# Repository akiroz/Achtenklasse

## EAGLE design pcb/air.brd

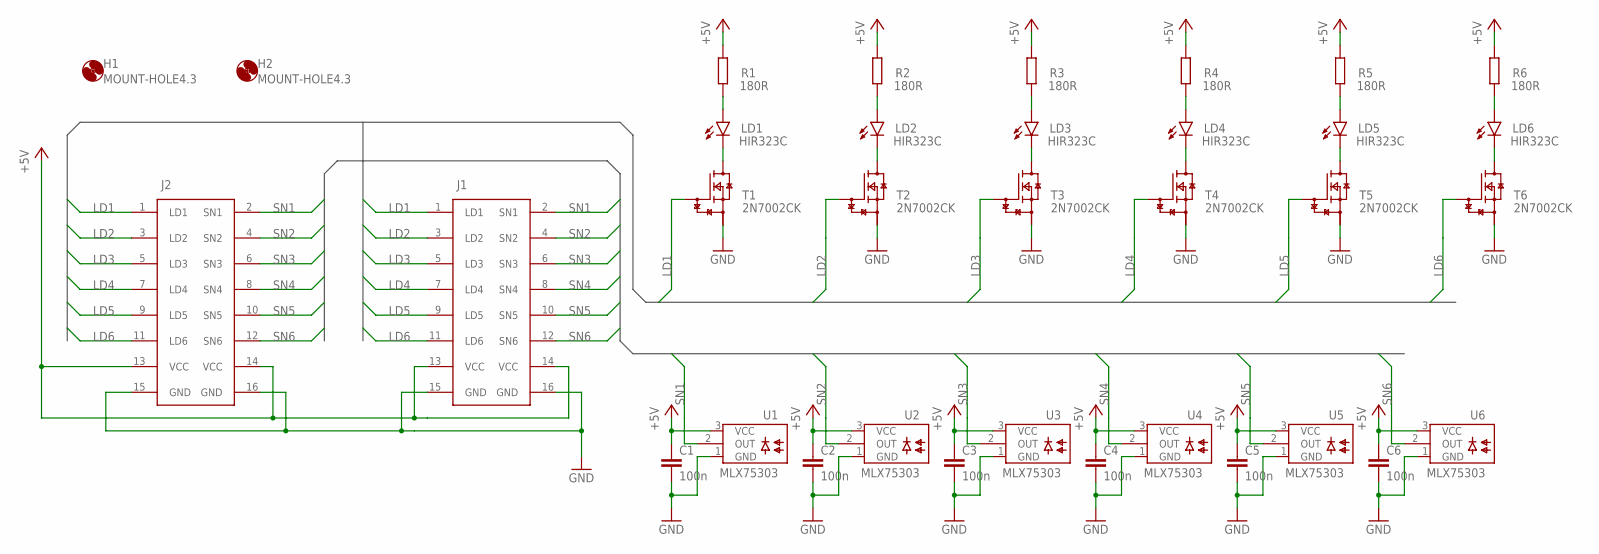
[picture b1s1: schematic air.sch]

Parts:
C1, C2, C3, C4, C5, C6: 100n; C0805K
H1, H2: MOUNT-HOLE4.3; 4,3
J1, J2: 2516-SMD-AIR; 612X1620621
LD1, LD2, LD3, LD4, LD5, LD6: HIR323C; LEDRD254W60D590H600B
R1, R2, R3, R4, R5, R6: 180R; R0805
T1, T2, T3, T4, T5, T6: 2N7002CK; SOT23
U1, U2, U3, U4, U5, U6: MLX75303; SOIC127P600X147-8N

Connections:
+5V: C1.1, C2.1, C3.1, C4.1, C5.1, C6.1, J1.13 (VCC), J1.14 (VCC), J2.13 (VCC), J2.14 (VCC), R1.2, R2.2, R3.2, R4.2, R5.2, R6.2, U1.3 (VCC), U2.3 (VCC), U3.3 (VCC), U4.3 (VCC), U5.3 (VCC), U6.3 (VCC)
GND: C1.2, C2.2, C3.2, C4.2, C5.2, C6.2, J1.15 (GND), J1.16 (GND), J2.15 (GND), J2.16 (GND), T1.2 (S), T2.2 (S), T3.2 (S), T4.2 (S), T5.2 (S), T6.2 (S), U1.1 (GND), U2.1 (GND), U3.1 (GND), U4.1 (GND), U5.1 (GND), U6.1 (GND)
LD1: J1.1 (LD1), J2.1 (LD1), T1.1 (G)
LD2: J1.3 (LD2), J2.3 (LD2), T2.1 (G)
LD3: J1.5 (LD3), J2.5 (LD3), T3.1 (G)
LD4: J1.7 (LD4), J2.7 (LD4), T4.1 (G)
LD5: J1.9 (LD5), J2.9 (LD5), T5.1 (G)
LD6: J1.11 (LD6), J2.11 (LD6), T6.1 (G)
unnamed: LD1.1 (A), R1.1
unnamed: LD1.2 (C), T1.3 (D)
unnamed: LD2.1 (A), R2.1
unnamed: LD2.2 (C), T2.3 (D)
unnamed: LD3.1 (A), R3.1
unnamed: LD3.2 (C), T3.3 (D)
unnamed: LD4.1 (A), R4.1
unnamed: LD4.2 (C), T4.3 (D)
unnamed: LD5.1 (A), R5.1
unnamed: LD5.2 (C), T5.3 (D)
unnamed: LD6.1 (A), R6.1
unnamed: LD6.2 (C), T6.3 (D)
SN1: J1.2 (SN1), J2.2 (SN1), U1.2 (OUT)
SN2: J1.4 (SN2), J2.4 (SN2), U2.2 (OUT)
SN3: J1.6 (SN3), J2.6 (SN3), U3.2 (OUT)
SN4: J1.8 (SN4), J2.8 (SN4), U4.2 (OUT)
SN5: J1.10 (SN5), J2.10 (SN5), U5.2 (OUT)
SN6: J1.12 (SN6), J2.12 (SN6), U6.2 (OUT)

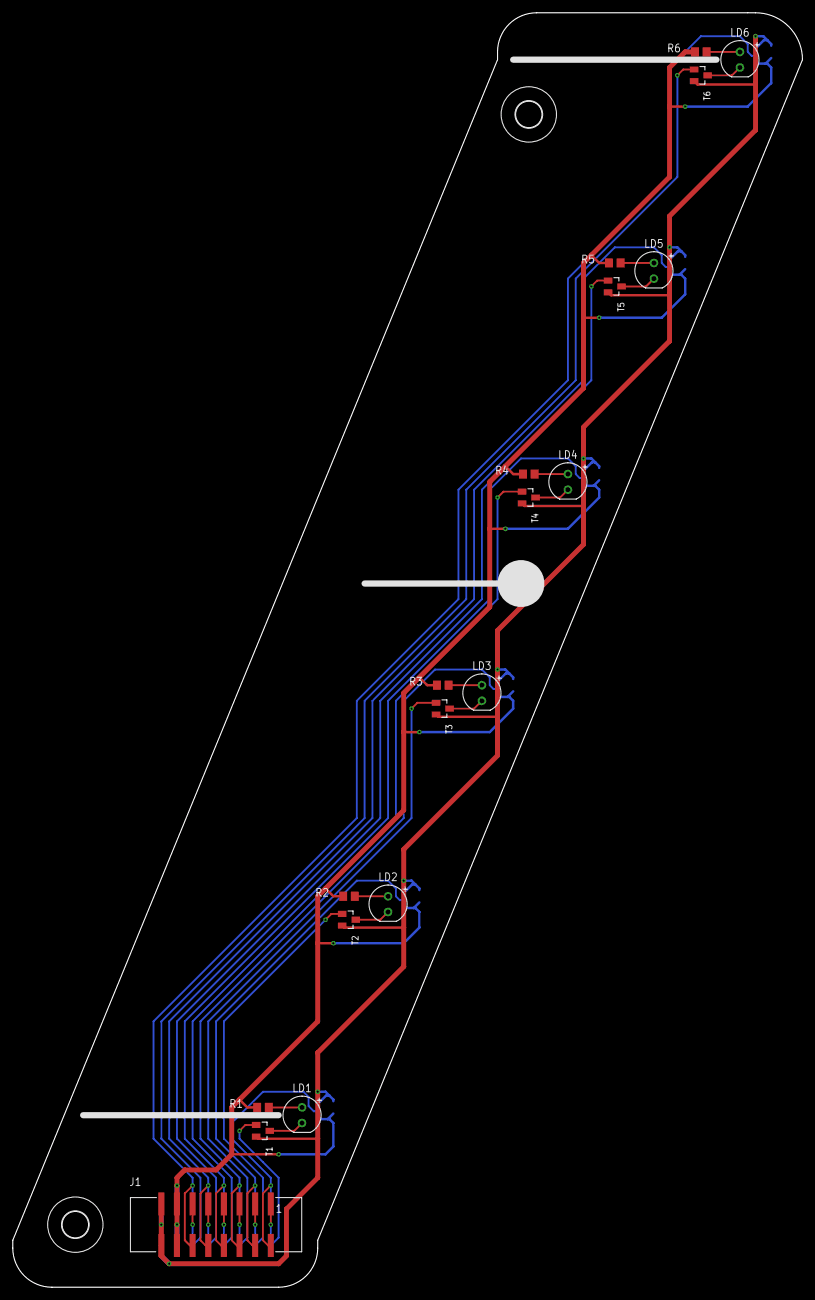
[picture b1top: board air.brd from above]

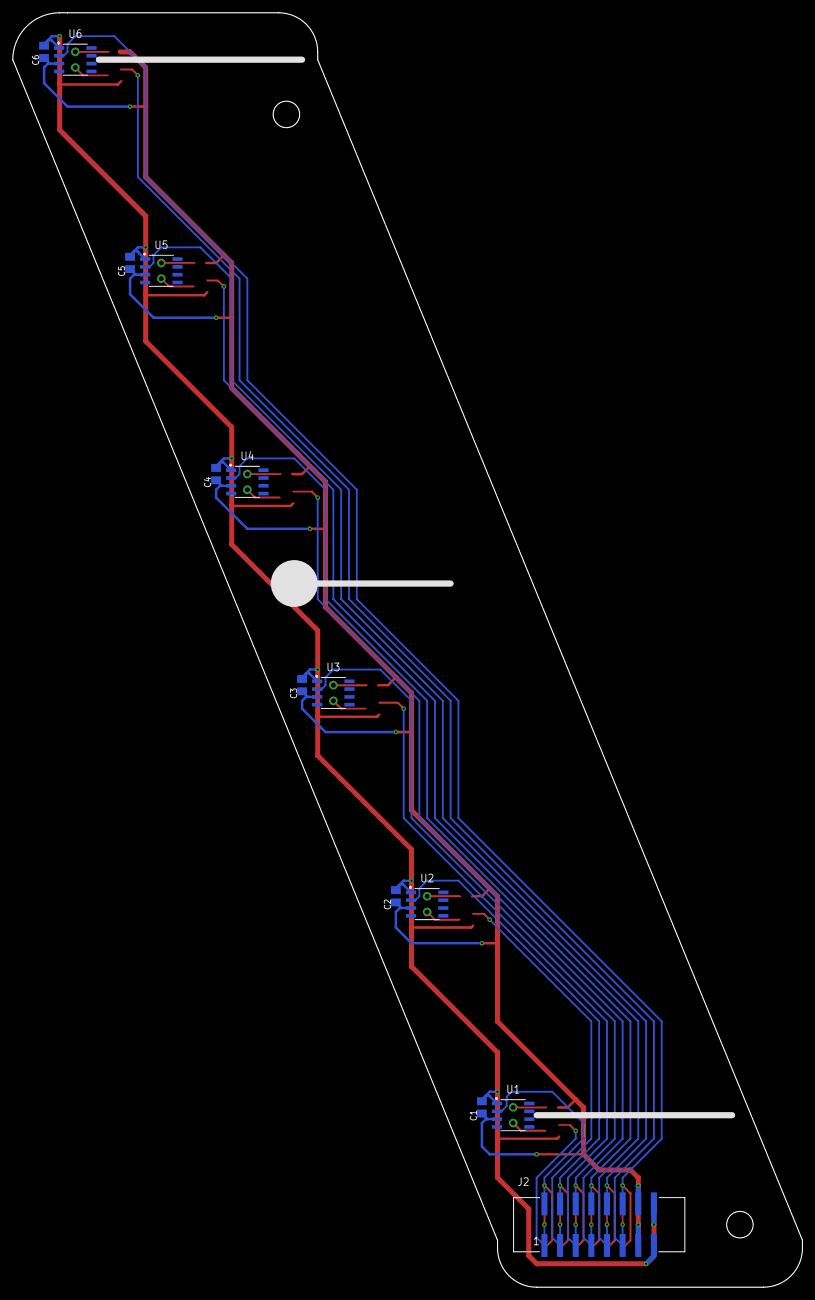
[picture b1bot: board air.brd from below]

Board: 2 copper layers, 128.3 x 207.0 mm, 34 parts (13 on the bottom side), 26 nets.

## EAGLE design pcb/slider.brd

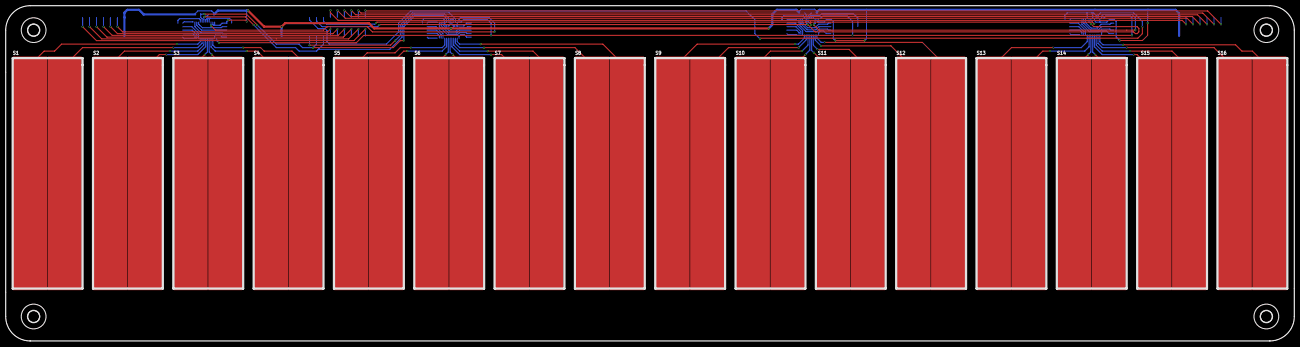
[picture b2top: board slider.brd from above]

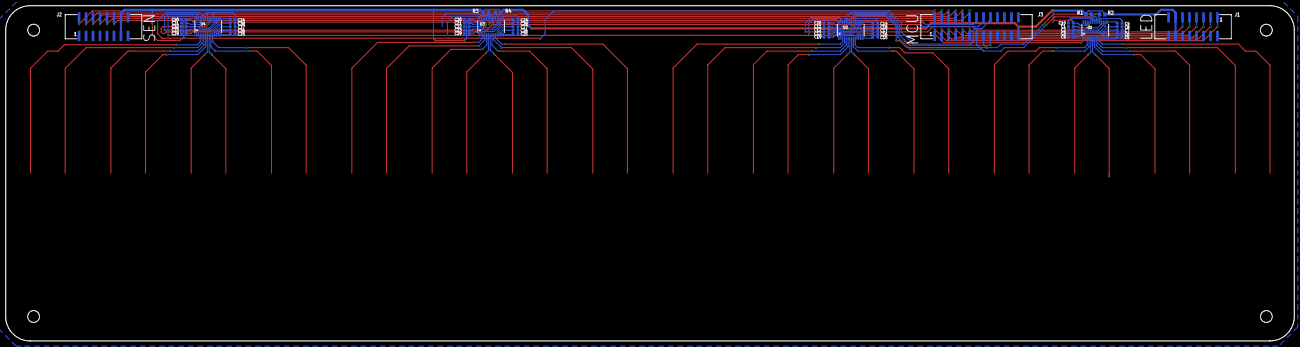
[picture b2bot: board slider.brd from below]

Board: 2 copper layers, 468.6 x 121.9 mm, 71 parts (51 on the bottom side), 91 nets.

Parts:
C1, C2, C3, C4, C5, C6, C7, C8, C9, C10, C11, C12, C13, C14, C15, C16, C17, C18, C19, C20, C21, C22, C23, C24, C25, C26, C27, C28, C29, C30, C31, C32, C33, C34, C35, C36, C37, C38, C39, C40: 100n; C0603K
H1, H2, H3, H4: MOUNT-HOLE4.3; 4,3
J1, J2: 612X1620621
J3: 612X2620621
R1, R2, R3, R4: 4.7k; R0805
S1, S2, S3, S4, S5, S6, S7, S8, S9, S10, S11, S12, S13, S14, S15, S16: SENSPAD
U1, U2, U3, U4: PCF8885TS; SOT361-1

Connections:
+5V: C10.1, C20.1, C30.1, C40.1, J1.13, J1.14, J2.13, J2.14, J3.25, R1.2, R2.2, R3.2, R4.2, U1.26, U1.27, U2.23, U2.26, U3.26, U3.27, U4.23, U4.26
GND: C1.2, C2.2, C3.2, C4.2, C5.2, C6.2, C7.2, C8.2, C9.2, C10.2, C11.2, C12.2, C13.2, C14.2, C15.2, C16.2, C17.2, C18.2, C19.2, C20.2, C21.2, C22.2, C23.2, C24.2, C25.2, C26.2, C27.2, C28.2, C29.2, C30.2, C31.2, C32.2, C33.2, C34.2, C35.2, C36.2, C37.2, C38.2, C39.2, C40.2, J1.15, J1.16, J2.15, J2.16, J3.26, U1.19, U1.22, U1.23, U1.24, U2.19, U2.22, U2.24, U3.19, U3.22, U3.23, U3.24, U4.19, U4.22, U4.24
INT1: J3.17, U2.25
INT2: J3.18, U4.25
LED1: J1.1, J3.1
LED2: J1.3, J3.3
LED3: J1.5, J3.5
LED4: J1.7, J3.7
LED5: J1.9, J3.9
LED6: J1.11, J3.11
unnamed: C1.1, U1.18
unnamed: C2.1, U1.17
unnamed: C3.1, U1.16
unnamed: C4.1, U1.15
unnamed: C5.1, U1.14
unnamed: C6.1, U1.13
unnamed: C7.1, U1.12
unnamed: C8.1, U1.11
unnamed: C11.1, U2.18
unnamed: C9.1, U1.2
unnamed: C12.1, U2.17
unnamed: C13.1, U2.16
unnamed: C14.1, U2.15
unnamed: C15.1, U2.14
unnamed: C16.1, U2.13
unnamed: C17.1, U2.12
unnamed: C18.1, U2.11
unnamed: C19.1, U2.2
unnamed: C21.1, U3.18
unnamed: C22.1, U3.17
unnamed: C23.1, U3.16
unnamed: C24.1, U3.15
unnamed: C25.1, U3.14
unnamed: C26.1, U3.13
unnamed: C27.1, U3.12
unnamed: C28.1, U3.11
unnamed: C29.1, U3.2
unnamed: C31.1, U4.18
unnamed: C32.1, U4.17
unnamed: C33.1, U4.16
unnamed: C34.1, U4.15
unnamed: C35.1, U4.14
unnamed: C36.1, U4.13
unnamed: C37.1, U4.12
unnamed: C38.1, U4.11
unnamed: C39.1, U4.2
unnamed: U1.1, U2.28, U3.28, U4.28
unnamed: U1.25, U2.27
unnamed: U3.25, U4.27
unnamed: S13.1, U4.10
unnamed: S13.2, U4.9
unnamed: S14.1, U4.8
unnamed: S14.2, U4.7
unnamed: S15.1, U4.6
unnamed: S15.2, U4.5
unnamed: S16.1, U4.4
unnamed: S16.2, U4.3
unnamed: S9.1, U3.10
unnamed: S9.2, U3.9
unnamed: S10.1, U3.8
unnamed: S10.2, U3.7
unnamed: S11.1, U3.6
unnamed: S11.2, U3.5
unnamed: S12.1, U3.4
unnamed: S12.2, U3.3
unnamed: S5.1, U2.10
unnamed: S5.2, U2.9
unnamed: S6.1, U2.8
unnamed: S6.2, U2.7
unnamed: S7.1, U2.6
unnamed: S7.2, U2.5
unnamed: S8.1, U2.4
unnamed: S8.2, U2.3
unnamed: S1.1, U1.10
unnamed: S1.2, U1.9
unnamed: S2.1, U1.8
unnamed: S2.2, U1.7
unnamed: S3.1, U1.6
unnamed: S3.2, U1.5
unnamed: S4.1, U1.4
unnamed: S4.2, U1.3
SCL1: J3.15, R2.1, U1.20, U2.20
SCL2: J3.16, R4.1, U3.20, U4.20
SDA1: J3.13, R1.1, U1.21, U2.21
SDA2: J3.14, R3.1, U3.21, U4.21
SEN1: J2.2, J3.2
SEN2: J2.4, J3.4
SEN3: J2.6, J3.6
SEN4: J2.8, J3.8
SEN5: J2.10, J3.10
SEN6: J2.12, J3.12

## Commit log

2019-12-09 PCB Design
2020-01-07 Add side panel
